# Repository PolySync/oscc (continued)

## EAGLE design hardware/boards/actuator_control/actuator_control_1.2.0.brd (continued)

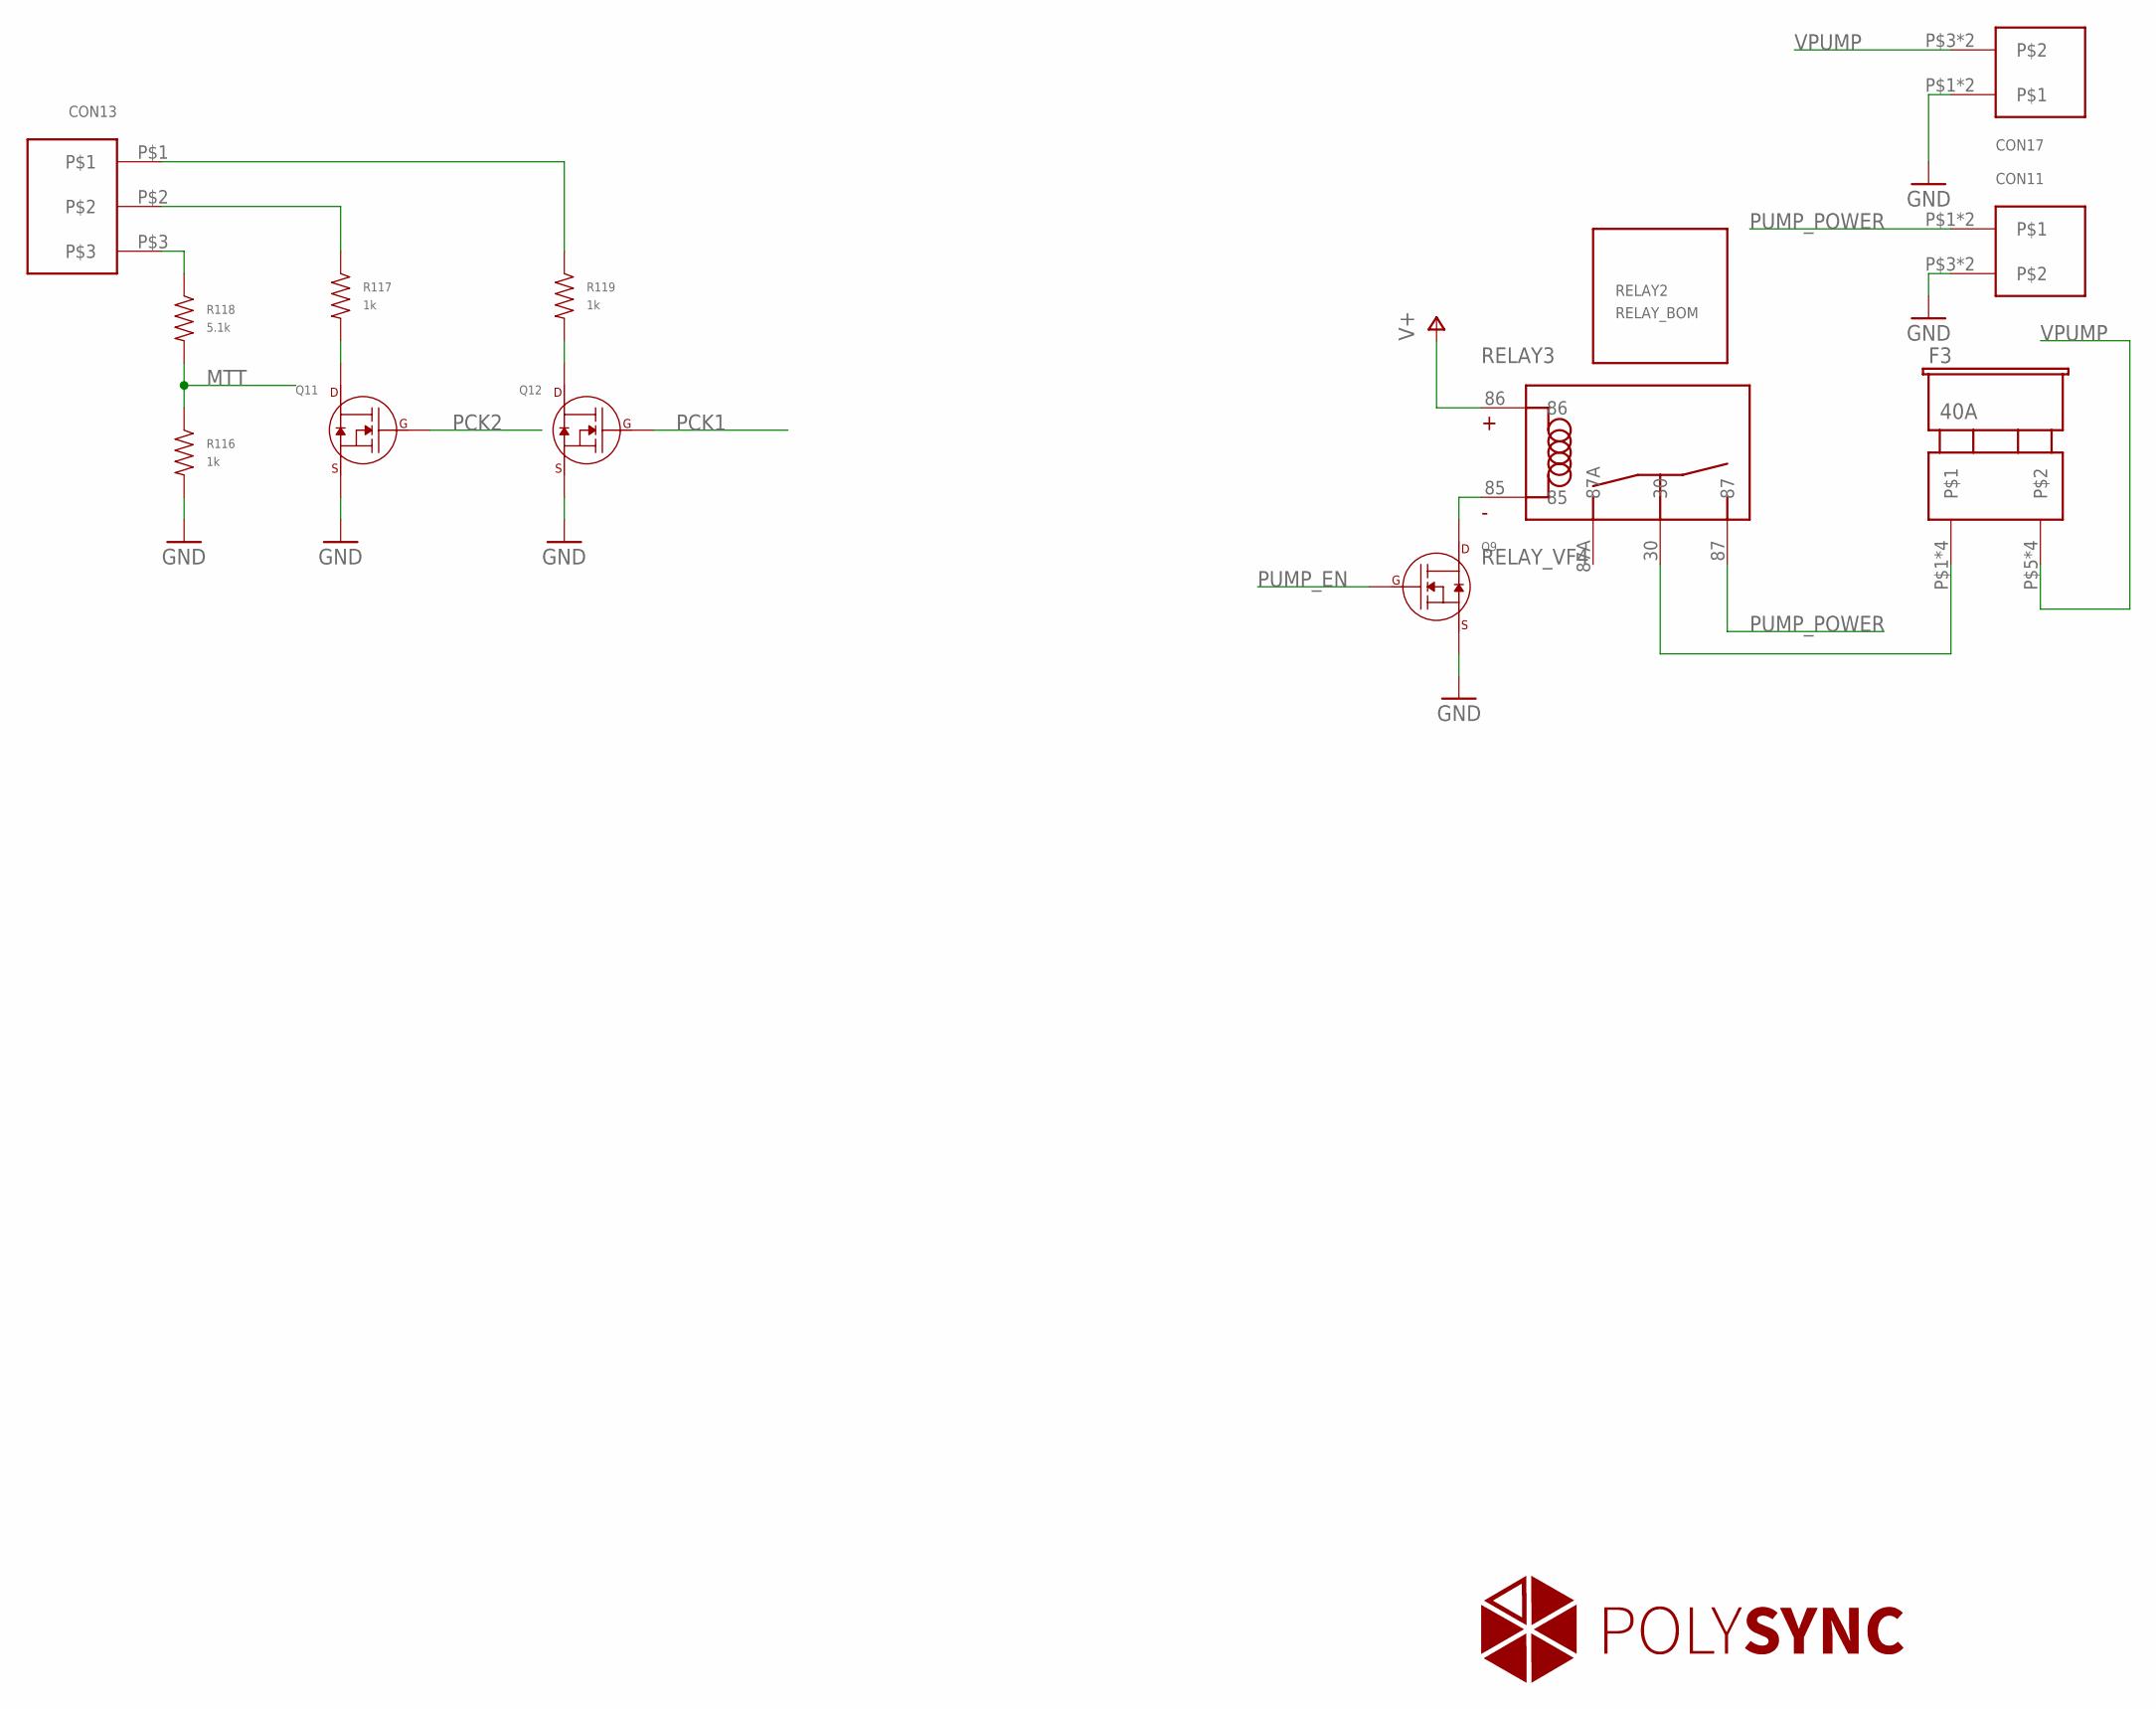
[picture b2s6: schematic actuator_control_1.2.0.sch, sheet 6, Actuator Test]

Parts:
CON11, CON17: CON210.16MM; PHOENIX_2_10.16MM; PARTNO 1773976
CON13: CON3; PHOENIX_3_45
F3: 40A; FUSE_ATO; PARTNO 178.6165.0001
Q9, Q11, Q12: N-CHANNEL_FET_SOT-23-3; SOT-23-3
R116, R117, R119: 1k; R0402
R118: 5.1k; R0402
RELAY2: RELAY_BOM; VCF4_RELAY; PARTNO 1432868-1
RELAY3: RELAY_VF4; VCF4-SOCKET; PARTNO VCF4-1000

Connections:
GND: CON11.P$3, CON11.P$4, CON17.P$1, CON17.P$2, Q9.P$2 (SOURCE), Q11.P$2 (SOURCE), Q12.P$2 (SOURCE), R116.P$2; also elsewhere on the board
MTT: R116.P$1, R118.P$2; also elsewhere on the board
unnamed: F3.P$1, F3.P$2, F3.P$3, F3.P$4, RELAY3.30
unnamed: Q9.P$3 (DRAIN), RELAY3.85
unnamed: CON13.P$3, R118.P$1
unnamed: CON13.P$2, R117.P$1
unnamed: CON13.P$1, R119.P$1
unnamed: Q11.P$3 (DRAIN), R117.P$2
unnamed: Q12.P$3 (DRAIN), R119.P$2
PCK1: Q12.P$1 (GATE); also elsewhere on the board
PCK2: Q11.P$1 (GATE); also elsewhere on the board
PUMP_EN: Q9.P$1 (GATE); also elsewhere on the board
PUMP_POWER: CON11.P$1, CON11.P$2, RELAY3.87
V+: RELAY3.86; also elsewhere on the board
VPUMP: CON17.P$3, CON17.P$4, F3.P$5, F3.P$6, F3.P$7, F3.P$8

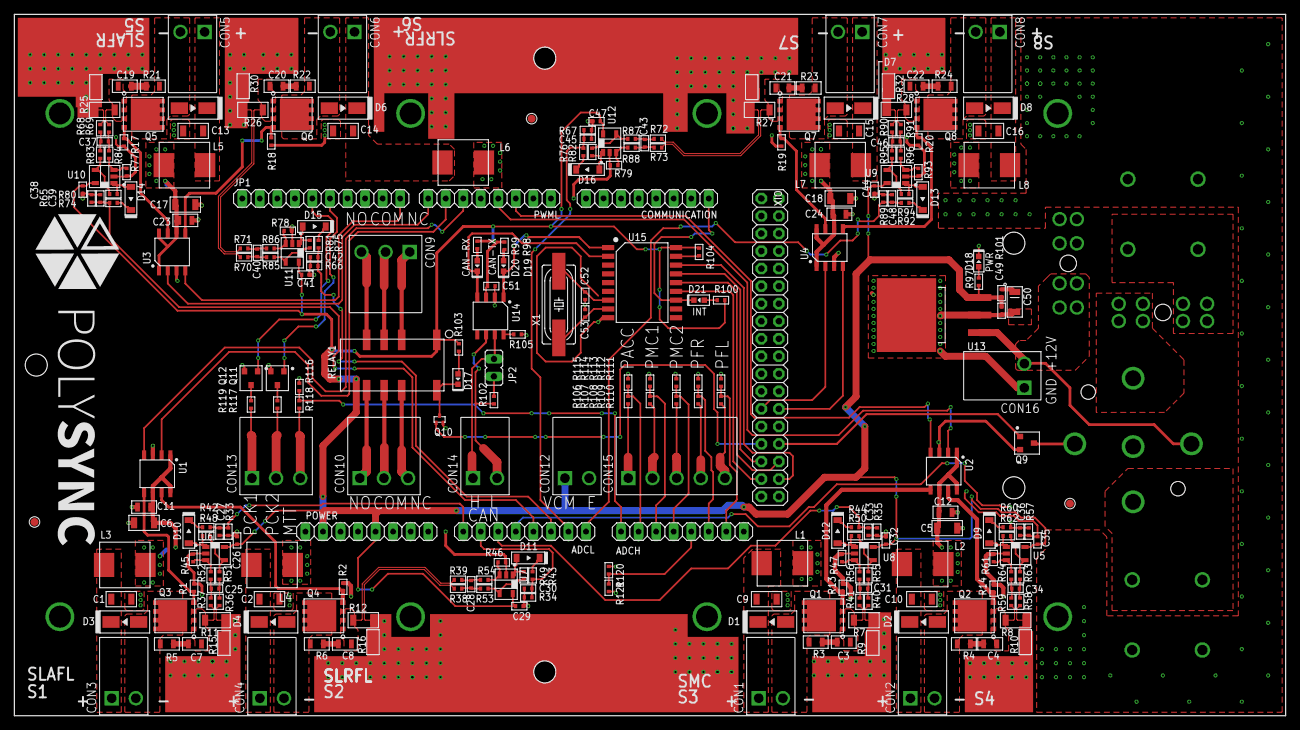
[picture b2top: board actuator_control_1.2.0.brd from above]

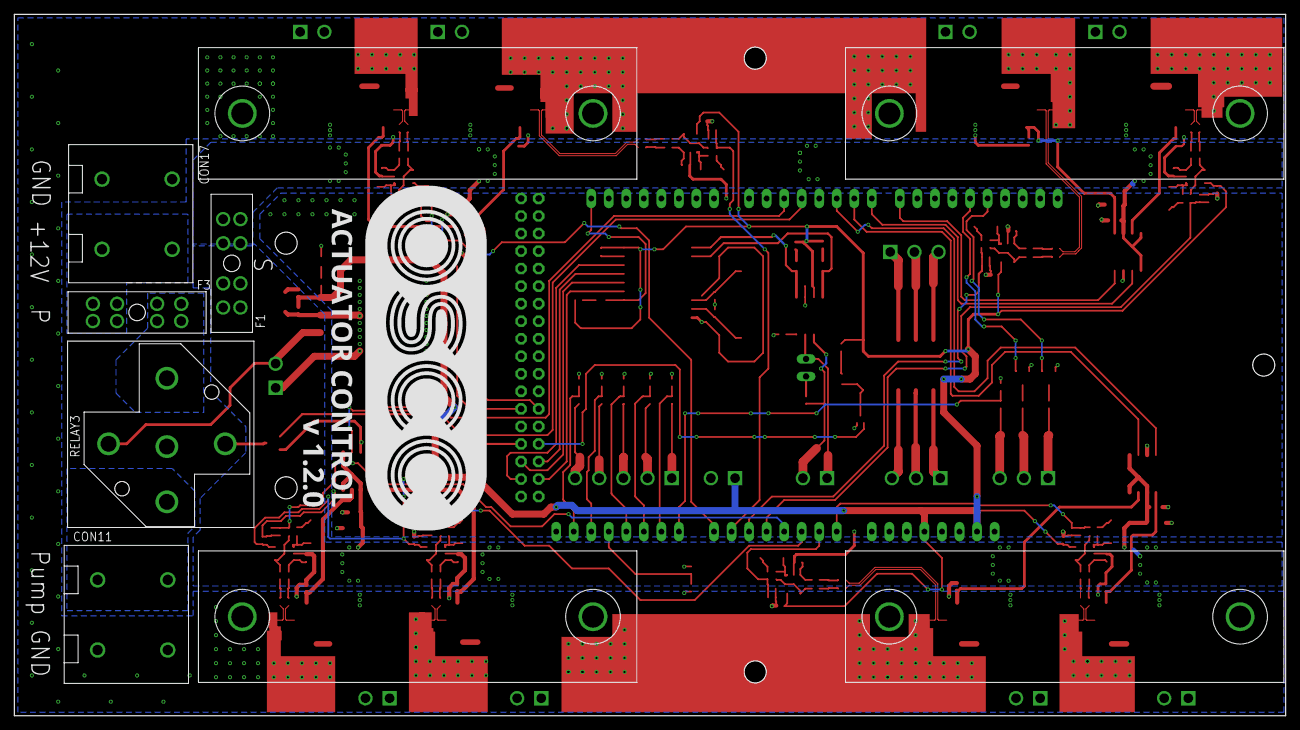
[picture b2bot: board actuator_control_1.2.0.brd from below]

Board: 2 copper layers, 184.2 x 101.6 mm, 270 parts (11 on the bottom side), 168 nets.

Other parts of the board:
U$3, U$7, U$9, U$10: HEATSINK_2X_75
U$11: POLYSYNC_ACT_1_2_0
U$13: POLYSYNC

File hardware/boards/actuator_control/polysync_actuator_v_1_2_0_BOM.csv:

Polysync Actuator Board BOM V1.2.0,,,,,,,,
,,,,,,,,
Quantity,Reference Designator,Description,Mfg,Mfg Part No.,Distributor,Distributor Part No.,Price,Total Price
8,"R7, R8, R11, R12, R25, R26, R27, R28",RES SMD 0.02 OHM 1% 1W 1206,Panasonic Electronic Components,ERJ-8CWFR020V,Digikey,P0.02BVCT-ND,0.69,5.52
1,R101,RES SMD 0.3 OHM 1% 1/6W 0402,Panasonic Electronic Components,ERJ-2BQFR30X,Digikey,P.30AKCT-ND,0.59,0.59
5,"R106, R107, R108, R109, R110",RES SMD 0.0OHM JUMPER 1/10W 0402,Panasonic Electronic Components,ERJ-2GE0R00X,Digikey,P0.0JCT-ND,0.1,0.5
8,"R9, R10, R15, R16, R29, R30, R31, R32",RES SMD 0.0 OHM JUMPER 1/8W 0805,Panasonic Electronic Components,ERJ-6GEY0R00V,Digikey,P0.0ACT-ND,0.1,0.8
8,"R3, R4, R5, R6, R21, R22, R23, R24",RES SMD 100 OHM 1% 1/8W 0805,Panasonic Electronic Components,ERJ-6ENF1000V,Digikey,P100CCT-ND,0.1,0.8
24,"R33, R34, R35, R45, R46, R47, R48, R49, R50, R57, R61, R62, R65, R66, R67, R77, R78, R79, R80, R81, R82, R89, R93, R94",RES SMD 100K OHM 1% 1/10W 0402,Panasonic Electronic Components,ERJ-2RKF1003X,Digikey,P100KLCT-ND,0.1,2.4
10,"R1, R2, R13, R14, R17, R18, R19, R20, R104, R121",RES SMD 10K OHM 1% 1/10W 0402,Panasonic Electronic Components,ERJ-2RKF1002X,Digikey,P10.0KLCT-ND,0.1,1
1,R102,RES SMD 120 OHM 1% 1/10W 0402,Panasonic Electronic Components,ERJ-2RKF1200X,Digikey,P120LCT-ND,0.1,0.1
48,"R36, R37, R38, R39, R40, R41, R42, R43, R44, R51, R52, R53, R54, R55, R56, R58, R59, R60, R63, R64, R68, R69, R70, R71, R72, R73, R74, R75, R76, R83, R84, R85, R86, R87, R88, R90, R91, R92, R95, R96, R97, R98, R99, R100, R103, R116, R117, R119",RES SMD 1K OHM 1% 1/10W 0402,Panasonic Electronic Components,ERJ-2RKF1001X,Digikey,P1.00KLCT-ND,0.1,4.8
2,"R105, R120",RES SMD 47K OHM 1% 1/10W 0402,Panasonic Electronic Components,ERJ-2RKF4702X,Digikey,P47.0KLCT-ND,0.1,0.2
1,R118,RES SMD 5.1K OHM 1% 1/10W 0402,Panasonic Electronic Components,ERJ-2RKF5101X,Digikey,P5.10KLCT-ND,0.1,0.1
18,"C26, C27, C29, C30, C32, C33, C35, C36, C38, C39, C41, C42, C44, C45, C47, C48, C49, C51",0.10µF ±10% 100V Ceramic Capacitor X5R 0402 (1005 Metric),Murata Electronics North America,GRM155R62A104KE14D,Digikey,490-10458-1-ND,0.1,1.8
12,"C3, C4, C7, C8, C11, C12, C19, C20, C21, C22, C23, C24",0.10µF ±10% 100V Ceramic Capacitor X7R 0805 (2012 Metric),"Samsung Electro-Mechanics America, Inc.",CL21B104KCFNNNE,Digikey,1276-6840-1-ND,0.1,1.2
8,"C25, C28, C31, C34, C37, C40, C43, C46","100pF ±5% 50V Ceramic Capacitor C0G, NP0 0402 (1005 Metric)",Yageo,CC0402JRNPO9BN101,Digikey,311-1024-1-ND,0.1,0.8
12,"C1, C2, C5, C6, C9, C10, C13, C14, C15, C16, C17, C18",1µF ±10% 100V Ceramic Capacitor X7R 1206 (3216 Metric),"Samsung Electro-Mechanics America, Inc.",CL31B105KCHNNNE,Digikey,1276-1838-1-ND,0.29,3.48
2,"C52, C53","22pF ±5% 50V Ceramic Capacitor C0G, NP0 0402 (1005 Metric)",Murata Electronics North America,GRM1555C1H220JA01J,Digikey,490-11382-1-ND,0.1,0.2
1,C50,33µF ±10% Molded Tantalum Capacitors 10V 1206 (3216 Metric) 1.7 Ohm,AVX Corporation,TAJA336K010RNJ,Digikey,478-8882-1-ND,0.6,0.6
3,"Q9, Q11, Q12",MOSFET N-CH 60V 6A,Toshiba Semiconductor and Storage,"SSM3K341R,LF",Digikey,SSM3K341RLFCT-ND,0.43,1.29
8,"Q1, Q2, Q3, Q4, Q5, Q6, Q7, Q8",MOSFET N-CH 60V 50A 8SON,Texas Instruments,CSD18537NQ5A,Digikey,296-36455-1-ND,0.85,6.8
1,Q10,MOSFET N-CH 20V 0.2A EMT3,Rohm Semiconductor,RE1C002UNTCL,Digikey,RE1C002UNTCLCT-ND,0.2,0.2
1,D21,Blue 470nm LED Indication - Discrete 3.2V 0603 (1608 Metric),Wurth Electronics Inc,150060BS75000,Digikey,732-4966-1-ND,0.26,0.26
2,"D17, D20",LED RED CLEAR 0603 SMD,Wurth Electronics Inc,150060RS75000,Digikey,732-4978-1-ND,0.24,0.48
2,"D18, D19",LED GREEN CLEAR 0603 SMD,Wurth Electronics Inc,150060GS75000,Digikey,732-4971-1-ND,0.24,0.48
8,"D1, D2, D3, D4, D5, D6, D7, D8",Diode Standard 100V 1A Surface Mount SMA,Diodes Incorporated,US1B-13-F,Digikey,US1B-FDICT-ND,0.42,3.36
8,"D9, D10, D11, D12, D13, D14, D15, D16",Diode Schottky 20V 500mA Surface Mount SOD-123,Diodes Incorporated,B0520LW-7-F,Digikey,B0520LW-FDICT-ND,0.32,2.56
8,"L1, L2, L3, L4, L5, L6, L7, L8",2.2µH Shielded Wirewound Inductor 10A 12 mOhm Max Nonstandard,Bourns Inc.,SRP7050TA-2R2M,Digikey,SRP7050TA-2R2MCT-ND,1.18,9.44
1,X1,16MHz ±30ppm Crystal 18pF 40 Ohm -40°C ~ 85°C Surface Mount HC49/US,Abracon LLC,ABLS-16.000MHZ-D-4-T,Digikey,535-13436-1-ND,0.24,0.24
1,U15,CAN Controller CAN 2.0 SPI Interface 18-SOIC,Microchip Technology,MCP2515-I/SO,Digikey,MCP2515-I/SO-ND,1.82,1.82
1,U14,1/1 Transceiver Half CAN 8-SOIC,Microchip Technology,MCP2551-I/SN,Digikey,MCP2551-I/SN-ND,1.02,1.02
8,"U5, U6, U7, U8, U9, U10, U11, U12",General Purpose Amplifier 1 Circuit Rail-to-Rail SOT-23-5,Texas Instruments,OPA170AIDBVT,Digikey,296-29496-1-ND,1.41,11.28
1,U13,Linear Voltage Regulator IC Positive Fixed 1 Output 5V 750mA DDPAK/TO-263-3,Texas Instruments,TL750M05CKTTR,Digikey,296-20776-1-ND,1.47,1.47
4,"U1, U2, U3, U4",Low-Side Gate Driver IC Non-Inverting 8-SOIC,Texas Instruments,UCC27524DR,Digikey,296-30129-1-ND,1.94,7.76
1,RELAY1,General Purpose Relay DPDT (2 Form C) Surface Mount,Kemet,EE2-5NU-L,Digikey,399-11017-1-ND,1.91,1.91
1,RELAY2,Automotive Relay SPDT (1 Form C) 12VDC Coil Through Hole,TE Connectivity Potter & Brumfield Relays,1432868-1,Digikey,PB1040-ND,3.46,3.46
1,RELAY3,Relay Socket Through Hole,TE Connectivity Potter & Brumfield Relays,VCF4-1000,Digikey,PB232-ND,1.8,1.8
1,JP2,"2 Positions Header, Unshrouded Connector 0.100"" (2.54mm) Through Hole Gold or Gold, GXT™",Amphenol FCI,77311-118-02LF,Digikey,609-4434-ND,0.18,0.18
1,JP1,"10 Positions Header, Unshrouded Connector 0.100"" (2.54mm) Through Hole Gold",Wurth Electronics Inc,61301011121,Digikey,732-2670-ND,1.01,1.01
1,XIO,"36 Positions Header, Unshrouded Connector 0.100"" (2.54mm) Through Hole Gold",Wurth Electronics Inc,61303621121,Digikey,732-5309-ND,1.64,1.64
5,"ADCH, ADCL, COMMUNICATION, POWER, PWML","8 Positions Header, Unshrouded Connector 0.100"" (2.54mm) Through Hole Gold",Wurth Electronics Inc,61300811121,Digikey,732-5321-ND,0.35,1.75
2,"CON11, CON17","2 Position Wire to Board Terminal Block Horizontal with Board 0.400"" (10.16mm) Through Hole",Phoenix Contact,1773976,Digikey,277-5761-ND,8.66,17.32
11,"CON1, CON2, CON3, CON4, CON5, CON6, CON7, CON8, CON12, CON14, CON16","2 Position Wire to Board Terminal Block 45° (135°) Angle with Board 0.138"" (3.50mm) Through Hole",Phoenix Contact,1988956,Digikey,277-1779-ND,0.41,4.51
3,"CON9, CON10, CON13","3 Position Wire to Board Terminal Block 45° (135°) Angle with Board 0.138"" (3.50mm) Through Hole",Phoenix Contact,1988969,Digikey,277-1780-ND,0.61,1.83
1,CON15,"5 Position Wire to Board Terminal Block 45° (135°) Angle with Board 0.138"" (3.50mm) Through Hole",Phoenix Contact,1988985,Digikey,277-1782-ND,0.97,0.97
2,"F1, F3",Fuse Holder 80V 1 Circuit Blade PCB,Littelfuse Inc.,178.6165.0001,Digikey,F5197-ND,3.24,6.48
,,,,,,,,
1,For F3,FUSE AUTO 40A 32VDC BLADE,Littelfuse Inc.,0257040.PXAPC,Digikey,F5952-ND,0.47,0.47
1,For F1,FUSE AUTOMOTIVE 20A 32VDC BLADE,Littelfuse Inc.,0287020.PXCN,Digikey,F4201-ND,0.28,0.28
1,For JP2,"2 (1 x 2) Position Shunt Connector White Open Top 0.100"" (2.54mm) Gold or Gold, GXT™",Amphenol FCI,68786-102LF,Digikey,609-3121-ND,0.19,0.19
Total,,,,,,,,$117.15

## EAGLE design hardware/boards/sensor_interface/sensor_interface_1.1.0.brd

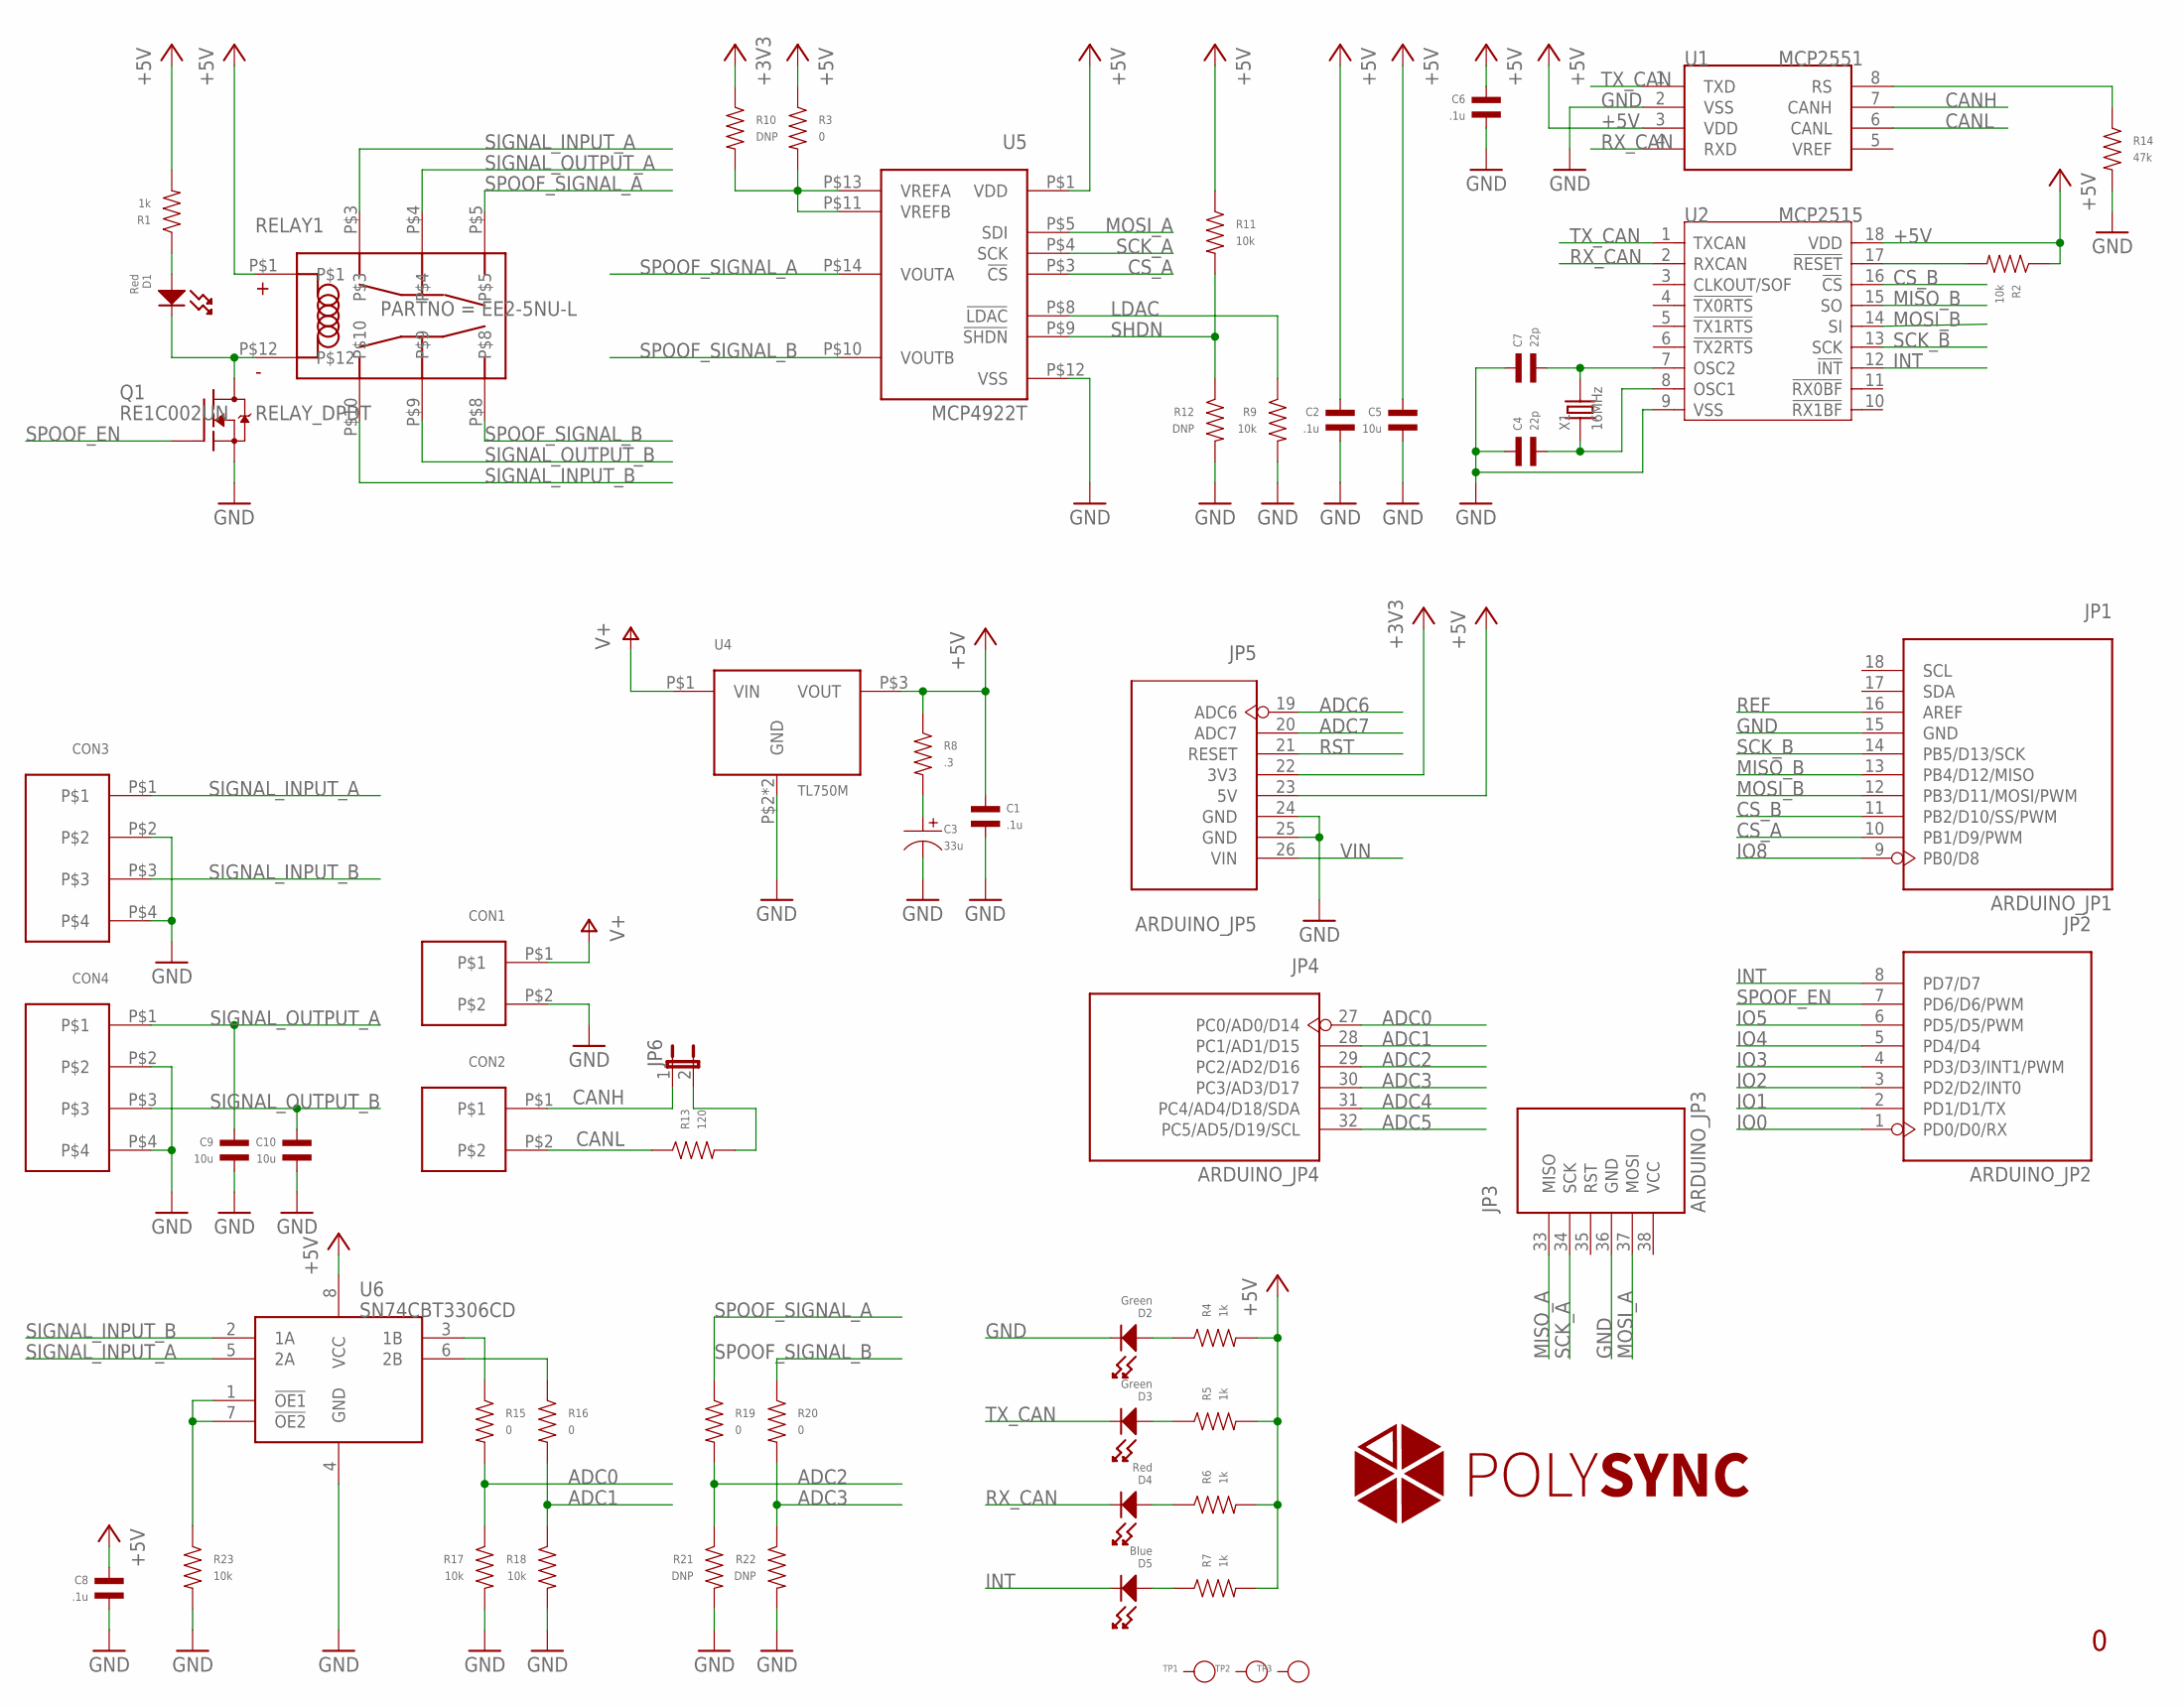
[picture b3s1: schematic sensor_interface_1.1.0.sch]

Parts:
C1, C2, C6, C8: .1u; C0402
C3: 33u; CP1206
C4, C7: 22p; C0402
C5, C9, C10: 10u; C0805
CON1, CON2: CON23.5MM; PHOENIX_2_45
CON3, CON4: CON4; PHOENIX_4_45
D1, D4: Red; LED0603
D2, D3: Green; LED0603
D5: Blue; LED0603
JP1: ARDUINO_JP1
JP2: ARDUINO_JP2
JP3: ARDUINO_JP3
JP4: ARDUINO_JP4
JP5: ARDUINO_JP5
JP6: JP1E; JP1
Q1: RE1C002UN; EMT3F
R1, R4, R5, R6, R7: 1k; R0402
R2, R9, R11, R17, R18, R23: 10k; R0402
R3, R15, R16, R19, R20: 0; R0402
R8: .3; R0402
R10, R12, R21, R22: DNP; R0402
R13: 120; R0402
R14: 47k; R0402
RELAY1: RELAY_DPDT; KEMET_EE2; PARTNO EE2-5NU-L
TP1, TP2, TP3: PAD-TEST-POINT'4545'; TP_4545
U1: MCP2551; SOIC8-6.0
U2: MCP2515; SOIC18
U4: TL750M; TO-263
U5: MCP4922T; TSSOP-14
U6: SN74CBT3306CD; SOIC-8
X1: 16MHz; HC49UP

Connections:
+3V3: JP5.22 (3V3), R10.P$1
+5V: C1.P$1, C2.P$1, C5.P$1, C6.P$1, C8.P$1, JP5.23 (5V), R1.P$2, R2.P$1, R3.P$1, R4.P$2, R5.P$2, R6.P$2, R7.P$2, R8.P$1, R11.P$1, RELAY1.P$1, U1.3 (VDD), U2.18 (VDD), U4.P$3 (VOUT), U5.P$1 (VDD), U6.8 (VCC)
ADC0: JP4.27 (PC0/AD0/D14), R15.P$2, R17.P$1
ADC1: JP4.28 (PC1/AD1/D15), R16.P$2, R18.P$1
ADC2: JP4.29 (PC2/AD2/D16), R19.P$2, R21.P$1
ADC3: JP4.30 (PC3/AD3/D17), R20.P$2, R22.P$1
ADC4: JP4.31 (PC4/AD4/D18/SDA)
ADC5: JP4.32 (PC5/AD5/D19/SCL)
ADC6: JP5.19 (ADC6)
ADC7: JP5.20 (ADC7)
CANH: CON2.P$1, JP6.1, U1.7 (CANH)
CANL: CON2.P$2, R13.P$1, U1.6 (CANL)
CS_A: JP1.10 (PB1/D9/PWM), U5.P$3 (!CS)
CS_B: JP1.11 (PB2/D10/SS/PWM), U2.16 (!CS)
GND: C1.P$2, C2.P$2, C3.P$2, C4.P$1, C5.P$2, C6.P$2, C7.P$1, C8.P$2, C9.P$2, C10.P$2, CON1.P$2, CON3.P$2, CON3.P$4, CON4.P$2, CON4.P$4, D2.CATHODE, JP1.15 (GND), JP3.36 (GND), JP5.24 (GND), JP5.25 (GND), Q1.P$2 (S), R9.P$2, R12.P$2, R14.P$2, R17.P$2, R18.P$2, R21.P$2, R22.P$2, R23.P$2, U1.2 (VSS), U2.9 (VSS), U4.P$2 (GND), U4.P$4 (GND), U5.P$12 (VSS), U6.4 (GND)
INT: D5.CATHODE, JP2.8 (PD7/D7), U2.12 (!INT)
IO0: JP2.1 (PD0/D0/RX)
IO1: JP2.2 (PD1/D1/TX)
IO2: JP2.3 (PD2/D2/INT0)
IO3: JP2.4 (PD3/D3/INT1/PWM)
IO4: JP2.5 (PD4/D4)
IO5: JP2.6 (PD5/D5/PWM)
IO8: JP1.9 (PB0/D8)
LDAC: R9.P$1, U5.P$8 (!LDAC)
MISO_A: JP3.33 (MISO)
MISO_B: JP1.13 (PB4/D12/MISO), U2.15 (SO)
MOSI_A: JP3.37 (MOSI), U5.P$5 (SDI)
MOSI_B: JP1.12 (PB3/D11/MOSI/PWM), U2.14 (SI)
unnamed: D3.ANODE, R5.P$1
unnamed: JP6.2, R13.P$2
unnamed: D1.CATHODE, Q1.P$3 (D), RELAY1.P$12
unnamed: C3.P$1, R8.P$2
unnamed: D4.ANODE, R6.P$1
unnamed: D2.ANODE, R4.P$1
unnamed: R3.P$2, R10.P$2, U5.P$11 (VREFB), U5.P$13 (VREFA)
unnamed: D5.ANODE, R7.P$1
unnamed: R14.P$1, U1.8 (RS)
unnamed: D1.ANODE, R1.P$1
unnamed: R23.P$1, U6.1 (!OE1), U6.7 (!OE2)
unnamed: R16.P$1, U6.6 (2B)
unnamed: R15.P$1, U6.3 (1B)
unnamed: C7.P$2, U2.7 (OSC2), X1.2
unnamed: C4.P$2, U2.8 (OSC1), X1.1
REF: JP1.16 (AREF)
RST: JP5.21 (RESET)
RST_N: R2.P$2, U2.17 (!RESET)
RX_CAN: D4.CATHODE, U1.4 (RXD), U2.2 (RXCAN)
SCK_A: JP3.34 (SCK), U5.P$4 (SCK)
SCK_B: JP1.14 (PB5/D13/SCK), U2.13 (SCK)
SHDN: R11.P$2, R12.P$1, U5.P$9 (!SHDN)
SIGNAL_INPUT_A: CON3.P$1, RELAY1.P$3, U6.5 (2A)
SIGNAL_INPUT_B: CON3.P$3, RELAY1.P$10, U6.2 (1A)
SIGNAL_OUTPUT_A: C9.P$1, CON4.P$1, RELAY1.P$4
SIGNAL_OUTPUT_B: C10.P$1, CON4.P$3, RELAY1.P$9
SPOOF_EN: JP2.7 (PD6/D6/PWM), Q1.P$1 (G)
SPOOF_SIGNAL_A: R19.P$1, RELAY1.P$5, U5.P$14 (VOUTA)
SPOOF_SIGNAL_B: R20.P$1, RELAY1.P$8, U5.P$10 (VOUTB)
TX_CAN: D3.CATHODE, U1.1 (TXD), U2.1 (TXCAN)
V+: CON1.P$1, U4.P$1 (VIN)
VIN: JP5.26 (VIN)

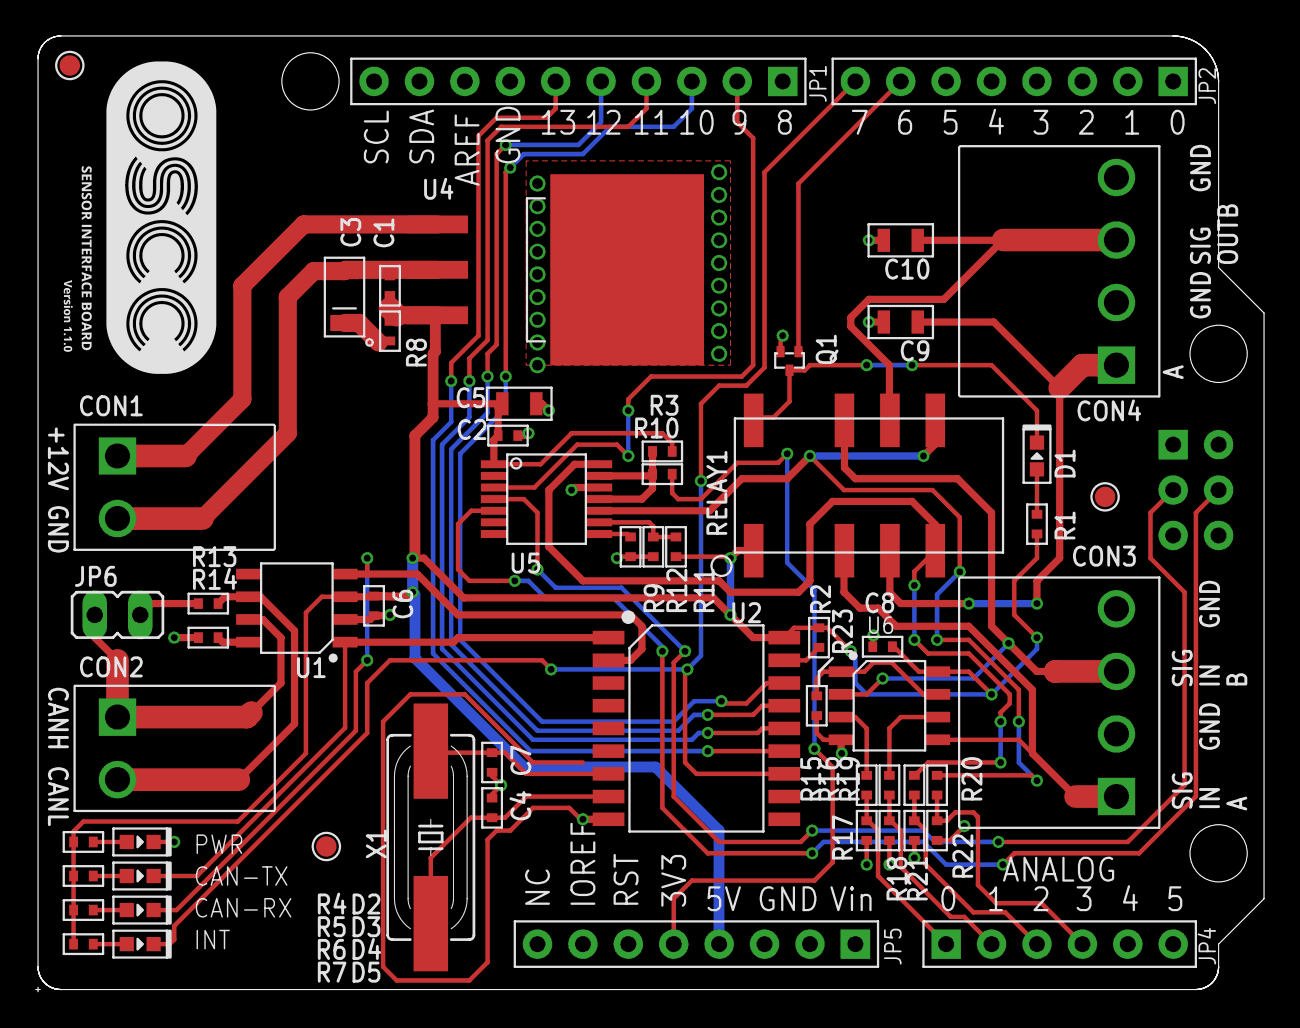
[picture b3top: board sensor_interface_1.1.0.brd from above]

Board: 2 copper layers, 68.6 x 53.3 mm, 61 parts (0 on the bottom side), 45 nets.

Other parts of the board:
U$1: POLYSYNC_STEERING_BOT
U$2: POLYSYNC_SENSOR_1_1_0

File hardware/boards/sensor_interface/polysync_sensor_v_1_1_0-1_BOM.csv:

Polysync Sensor BOM v1.1.0,,,,,,,,
,,,,,,,,
Quantity,Reference Designator,Description,Mfg,Mfg Part No.,Distributor,Distributor Part No.,Price,Total Price
1,R8,RES SMD 0.3 OHM 1% 1/6W 0402,Panasonic Electronic Components,ERJ-2BQFR30X,Digikey,P.30AKCT-ND,0.59,0.59
5,"R3, R15, R16, R19, R20",RES SMD 0.0OHM JUMPER 1/10W 0402,Panasonic Electronic Components,ERJ-2GE0R00X,Digikey,P0.0JCT-ND,0.1,0.5
6,"R2, R9, R11, R17, R18, R23",RES SMD 10K OHM 1% 1/10W 0402,Panasonic Electronic Components,ERJ-2RKF1002X,Digikey,P10.0KLCT-ND,0.1,0.6
1,R13,RES SMD 120 OHM 1% 1/10W 0402,Panasonic Electronic Components,ERJ-2RKF1200X,Digikey,P120LCT-ND,0.1,0.1
5,"R1, R4, R5, R6, R7",RES SMD 1K OHM 1% 1/10W 0402,Panasonic Electronic Components,ERJ-2RKF1001X,Digikey,P1.00KLCT-ND,0.1,0.5
1,R14,RES SMD 47K OHM 1% 1/10W 0402,Panasonic Electronic Components,ERJ-2RKF4702X,Digikey,P47.0KLCT-ND,0.1,0.1
4,"C1, C2, C6, C8",0.10µF ±10% 16V Ceramic Capacitor X7R 0402 (1005 Metric),Murata Electronics North America,GRM155R71C104KA88J,Digikey,490-6328-1-ND,0.1,0.4
3,"C5, C9, C19",10µF ±10% 10V Ceramic Capacitor X7R 0805 (2012 Metric),Taiyo Yuden,LMK212B7106KG-TD,Digikey,587-2668-1-ND,0.28,0.84
2,"C4, C7","22pF ±5% 50V Ceramic Capacitor C0G, NP0 0402 (1005 Metric)",Murata Electronics North America,GRM1555C1H220JA01J,Digikey,490-11382-1-ND,0.1,0.2
1,C3,33µF ±10% Molded Tantalum Capacitors 10V 1206 (3216 Metric) 1.7 Ohm,AVX Corporation,TAJA336K010RNJ,Digikey,478-8882-1-ND,0.6,0.6
1,D5,Blue 470nm LED Indication - Discrete 3.2V 0603 (1608 Metric),Wurth Electronics Inc,150060BS75000,Digikey,732-4966-1-ND,0.26,0.26
2,"D1, D4",LED RED CLEAR 0603 SMD,Wurth Electronics Inc,150060RS75000,Digikey,732-4978-1-ND,0.24,0.48
2,"D2, D3",LED GREEN CLEAR 0603 SMD,Wurth Electronics Inc,150060GS75000,Digikey,732-4971-1-ND,0.24,0.48
1,X1,16MHz ±30ppm Crystal 18pF 40 Ohm -40°C ~ 85°C Surface Mount HC49/US,Abracon LLC,ABLS-16.000MHZ-D-4-T,Digikey,535-13436-1-ND,0.24,0.24
1,Q1,MOSFET N-CH 20V 0.2A EMT3,Rohm Semiconductor,RE1C002UNTCL,Digikey,RE1C002UNTCLCT-ND,0.2,0.2
1,U2,CAN Controller CAN 2.0 SPI Interface 18-SOIC,Microchip Technology,MCP2515-I/SO,Digikey,MCP2515-I/SO-ND,1.82,1.82
1,U1,1/1 Transceiver Half CAN 8-SOIC,Microchip Technology,MCP2551-I/SN,Digikey,MCP2551-I/SN-ND,1.02,1.02
1,U5,12 Bit Digital to Analog Converter 2 14-TSSOP,Microchip Technology,MCP4922T-E/ST,Digikey,MCP4922T-E/STCT-ND,2.62,2.62
1,U4,Linear Voltage Regulator IC Positive Fixed 1 Output 5V 750mA DDPAK/TO-263-3,Texas Instruments,TL750M05CKTTR,Digikey,296-20776-1-ND,1.47,1.47
1,U6,IC SWITCH BUS DUAL FET 8-SOIC,Texas Instruments,SN74CBT3306CDR,Digikey,296-19215-1-ND,0.6,0.6
1,RELAY1,General Purpose Relay DPDT (2 Form C) Surface Mount,Kemet,EE2-5NU-L,Digikey,399-11017-1-ND,1.91,1.91
1,JP1,"10 Positions Header, Unshrouded Connector 0.100"" (2.54mm) Through Hole Gold or Gold, GXT™",Amphenol FCI,68002-210HLF,Digikey,609-3301-ND,0.44,0.44
2,"JP2, JP5","8 Positions Header, Unshrouded Connector 0.100"" (2.54mm) Through Hole Gold or Gold, GXT™",Amphenol FCI,68000-208HLF,Digikey,609-3257-ND,0.43,0.86
1,JP3,"6 Position Receptacle Connector 0.100"" (2.54mm) Through Hole Gold",Amphenol FCI,68683-303LF,Digikey,609-3582-ND,1.61,1.61
1,JP4,"6 Positions Header, Unshrouded Connector 0.100"" (2.54mm) Through Hole Gold or Gold, GXT™",Amphenol FCI,68000-206HLF,Digikey,609-3256-ND,0.32,0.32
1,JP6,"2 Positions Header, Unshrouded Connector 0.100"" (2.54mm) Through Hole Gold or Gold, GXT™",Amphenol FCI,77311-118-02LF,Digikey,609-4434-ND,0.18,0.18
2,"CON1, CON2","2 Position Wire to Board Terminal Block 45° (135°) Angle with Board 0.138"" (3.50mm) Through Hole",Phoenix Contact,1988956,Digikey,277-1779-ND,0.41,0.82
2,"CON3, CON4","4 Position Wire to Board Terminal Block 45° (135°) Angle with Board 0.138"" (3.50mm) Through Hole",Phoenix Contact,1988972,Digikey,277-1781-ND,0.82,1.64
1,For JP6,"2 (1 x 2) Position Shunt Connector White Open Top 0.100"" (2.54mm) Gold or Gold, GXT™",Amphenol FCI,68786-102LF,Digikey,609-3121-ND,0.19,0.19
Total,,,,,,,,$21.59

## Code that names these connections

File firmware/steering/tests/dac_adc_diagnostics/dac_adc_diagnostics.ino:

#include "SPI.h"
#include "mcp_can.h"
#include "can_frame.h"
#include "DAC_MCP49xx.h"
#include "common.h"




#define SIGNAL_INPUT_A A0     // input pin for sensing sensor 1 output

#define SIGNAL_INPUT_B A1     // input pin for sensing sensor 2 output

#define SPOOF_SIGNAL_A A2     // input pin for sensing DAC 1 output

#define SPOOF_SIGNAL_B A3     // input pin for sensing DAC 2 output

#define SPOOF_ENGAGE 6        // signal interrupt (relay) for spoofed signals

#define DAC_CS 9              // chip select pin for DAC

#define CAN_CS 10             // chip select pin for CAN


DAC_MCP49xx dac( DAC_MCP49xx::MCP4922, 9 ); // DAC model, SS pin, LDAC pin

// Construct the CAN shield object
MCP_CAN CAN( CAN_CS );


static void init_serial( void )
{
    Serial.begin( SERIAL_BAUD );
}


static void init_can ( void )
{
    // wait until we have initialized
    while( CAN.begin(CAN_BAUD) != CAN_OK )
    {
        // wait a little
        delay( CAN_INIT_RETRY_DELAY );
        Serial.println( "init_can: retrying" );
    }

    // debug log
    Serial.println( "init_can: pass" );
}



//BENCH TESTS


// the two DACS have circuitry for measuring the output. Create a signal and
// measure that the output is what is expected.
void test_DACS( )
{
    uint16_t dac_value;
    uint16_t dac_val_a;
    uint16_t dac_val_b;

    uint16_t spoof_a_adc_signal = 0;
    uint16_t spoof_b_adc_signal = 0;

    float spoof_a_adc_volts = 0.0;
    float spoof_b_adc_volts = 0.0;

    float dac_expected_output_a = 0.0;
    float dac_expected_output_b = 0.0;

    // energize the relay so we can read the values at the terminal
    digitalWrite( SPOOF_ENGAGE, HIGH );

    for ( dac_value = 0; dac_value < 4095; dac_value = dac_value + 15 )
    {
        dac_val_a = dac_value;
        dac_val_b = 4095.0 - dac_value;

        // Convert 12-bit DAC output integer value to volts ( 5V / 4096steps )
        // Maximum voltage is 5 Volts.
        dac_expected_output_a = ( 5.0 / 4095.0 ) * dac_val_a;
        dac_expected_output_b = ( 5.0 / 4095.0 ) * dac_val_b;

        dac.outputA( dac_val_a );
        dac.outputB( dac_val_b );

        delay( 2000 );

        spoof_a_adc_signal = analogRead( SPOOF_SIGNAL_A );
        spoof_b_adc_signal = analogRead( SPOOF_SIGNAL_B );

        // Convert 10-bit ADC input integer value to volts ( 5V / 1024steps )
        // Maximum voltage is 5 Volts.
        spoof_a_adc_volts = ( spoof_a_adc_signal * 5.0 ) / 1023.0;
        spoof_b_adc_volts = ( spoof_b_adc_signal * 5.0 ) / 1023.0;

        Serial.print( "DAC Value (A): " );
        Serial.print( dac_val_a );

        Serial.print( "\tDAC Value (B): " );
        Serial.print( dac_val_b );

        Serial.print( "\tOutput A Voltage: " );
        Serial.print( dac_expected_output_a, 3 );

        Serial.print( "\tOutput B Voltage: " );
        Serial.println( dac_expected_output_b, 3 );

        Serial.print( "Spoof A Value: " );
        Serial.print( spoof_a_adc_signal );

        Serial.print( "\tSpoof B Value: " );
        Serial.print( spoof_b_adc_signal );

        Serial.print( "\tSpoof A Voltage: " );
        Serial.print( spoof_a_adc_volts, 3 );

        Serial.print( "\tSpoof B Voltage: " );
        Serial.println( spoof_b_adc_volts, 3 );

        Serial.println( "" );
    }
}


void setup( )
{
    init_serial();
    init_can();
}


void loop()
{
    test_DACS();
    //test_interrupt_relay();
    //test_CAN_send();
    //test_CAN_recieve();
    //test_signal_sense();

}
